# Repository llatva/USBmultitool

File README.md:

# USBmultitool
USB multitool (2 USB ports from HUB, 1xRS232/TTL serial, radio interface w/gpio)

Schematic (analog section): Veli-Matti OH7JEV & Eero OH2BTG & co commenting the schematic at OH2K club

Layout design : Lasse OH3HZB (me)

Licensed under CC-BY 4.0, see https://creativecommons.org/licenses/by/4.0/

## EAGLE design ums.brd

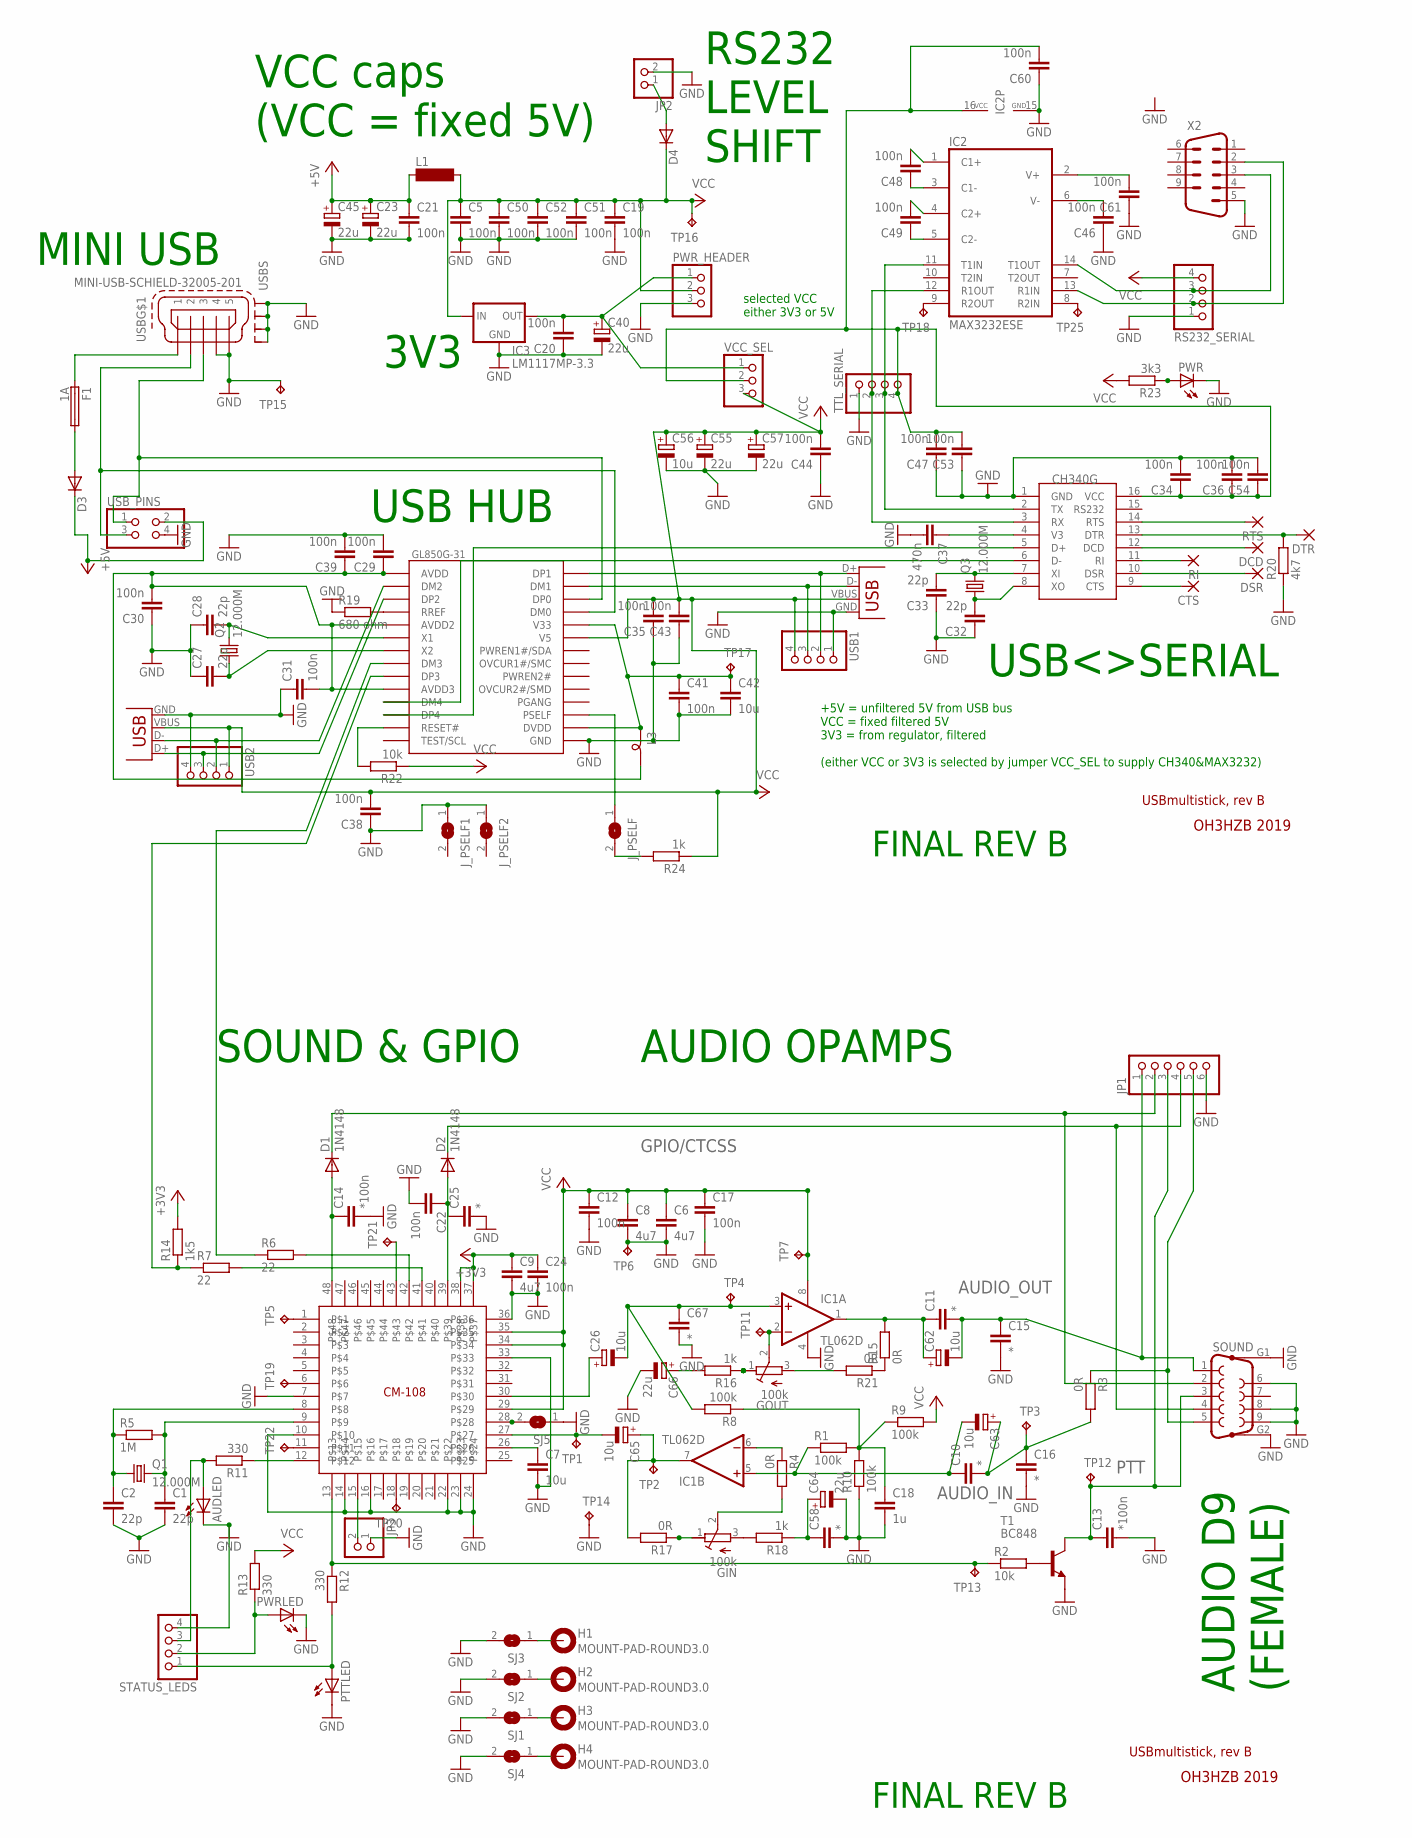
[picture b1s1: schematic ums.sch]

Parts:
AUDLED: LED3MM
C1, C2, C27, C28, C32, C33: 22p; C1206K
C5, C12: 100n; C1206K
C6, C8, C9: 4u7; C1206K
C7: 10u; C1206K
C10, C11, C16, C58: *; C1206K
C13, C14: *100n; C1206K
C15, C25, C67: *; C0805
C17, C19, C20, C21, C22, C24, C29, C30, C34, C35, C36, C38, C39, C41, C43, C44, C46, C47, C48, C49, C50, C51, C52, C53, C60, C61: 100n; C0805
C18: 1u; C4532
C23, C45: 22u; D/7343-31W
C26, C62, C63, C65: 10u; 153CLV-0605
C31, C54: 100n; C1206
C37: 470n; C0805
C40: 22u; SMC_B
C42: 10u; C0805
C55: 22u; C/6032-28R
C56: 10u; SMC_B
C57: 22u; CT6032
C64, C66: 22u; 153CLV-0605
CTS: SMD2; SMD1,27-2,54
D1: 1N4148; SOD123
D2: 1N4148; SOD323-W
D3, D4: DIODE-DO214AC; DO214AC
DCD: SMD2; SMD1,27-2,54
DSR: SMD2; SMD1,27-2,54
DTR: SMD2; SMD1,27-2,54
F1: 1A; TE5
GIN: 100k; RTRIMT93YA
GOUT: 100k; RTRIMT93YA
H1, H2, H3, H4: MOUNT-PAD-ROUND3.0; 3,0-PAD
IC1: TL062D; SO08
IC2: MAX3232ESE; SO16
IC3: LM1117MP-3.3; SOT223
IC4: GL850G-31; TSSOP28
JP1: PINHD-1X6; 1X06
JP2, JP3: PINHD-1X2; 1X02
J_PSELF, J_PSELF1, J_PSELF2: SJ
L1: SM-1206
L3: SM-B5
PTTLED: LED3MM
PWR: LEDCHIPLED_0805; CHIPLED_0805
PWRLED: LED3MM
PWR_HEADER: PINHD-1X3; 1X03
Q1, Q2, Q3: 12.000M; SM49
R1, R8, R9, R10: 100k; R1206
R2, R22: 10k; R1206
R3, R4, R15, R17, R21: 0R; R1206
R5: 1M; R1206
R6, R7: 22; R1206
R11, R12, R13: 330; R1206
R14: 1k5; R1206
R16, R18: 1k; R1206
R19: 680 ohm; R0805
R20: 4k7; R0805
R23: 3k3; R0805
R24: 1k; R0805
RI: SMD2; SMD1,27-2,54
RS232_SERIAL: PINHD-1X4; 1X04
RTS: SMD2; SMD1,27-2,54
SJ1, SJ2, SJ3, SJ4, SJ5: SJ
SOUND: F09HP
STATUS_LEDS: PINHD-1X4; 1X04
T1: BC848; SOT23-BEC
TP1, TP2, TP3, TP4, TP5, TP6, TP7, TP11, TP12, TP13, TP14, TP15, TP16, TP17, TP18, TP19, TP20, TP21, TP22, TP25: TPB1,27; B1,27
TTL_SERIAL: PINHD-1X4; 1X04
U$1: CM-108; LQFP-48
U$6: CH340G; SOIC16
USB: MINI-USB-SCHIELD-32005-201; 32005-201
USB1, USB2: PINHD-1X4; 1X04
USB-P1, USB-P2: USB-A-H
USB_PINS: PINHD-2X2; 2X02
VCC_SEL: PINHD-1X3; 1X03
X2: M09HP

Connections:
+3V3: C9.1, C24.1, R14.2, U$1.37, U$1.38
+5V: C21.1, C23.+, C45.+, D3.C, L1.1, USB_PINS.2
AUDIO_IN: C10.2, C16.1, C63.+, R3.2, TP3.TP
AUDIO_OUT: C11.2, C15.1, C62.-, JP1.1, SOUND.1
CM108-USB-DMINUS: IC4.8 (DM3), R6.1
CM108-USB-DPLUS: IC4.9 (DP3), R7.1, R14.1
GND: AUDLED.K (C), C1.2, C2.2, C5.2, C6.2, C7.2, C8.2, C9.2, C12.2, C13.2, C14.2, C15.2, C16.2, C17.2, C18.2, C19.2, C20.1, C21.2, C22.2, C23.-, C24.2, C25.2, C27.1, C28.1, C29.2, C30.1, C31.1, C32.1, C33.1, C34.2, C35.1, C36.2, C37.2, C38.1, C39.2, C40.-, C41.2, C42.2, C43.1, C44.1, C45.-, C46.1, C47.1, C50.2, C51.2, C52.2, C53.1, C54.2, C55.-, C56.-, C57.-, C58.2, C60.1, C61.1, C64.-, C66.-, C67.2, IC1.4 (V-), IC2.15 (GND), IC3.1 (GND), IC4.15 (GND), JP1.6, JP2.2, JP3.1, J_PSELF1.1, J_PSELF2.1, PTTLED.K (C), PWR.C, PWRLED.K (C), PWR_HEADER.3, R10.1, R19.1, R20.1, RS232_SERIAL.1, SJ1.2, SJ2.2, SJ3.2, SJ4.2, SJ5.1, SOUND.6, SOUND.8, SOUND.9, SOUND.G1, SOUND.G2, STATUS_LEDS.4, T1.E, TP6.TP, TP14.TP, TP15.TP, TTL_SERIAL.1, U$1.7, U$1.10, U$1.14, U$1.16, U$1.22, U$1.23, U$1.24, U$1.33, U$1.36, U$6.1 (GND), USB.4, USB.5, USB.M1 (S1), USB.M2 (S2), USB.M3 (S3), USB.M4 (S4), USB1.1, USB2.4, USB-P1.GND, USB-P2.GND, USB_PINS.4, X2.5
GPIO/CTCSS: D2.C, JP1.4, SOUND.4
JUMPER_SELECTED_VCC: C34.1, C36.1, C47.2, C53.2, C54.1, C60.2, IC2.16 (VCC), TTL_SERIAL.4, U$6.16 (VCC), VCC_SEL.2
unnamed: IC2.11 (T1IN), TTL_SERIAL.3, U$6.2 (TX)
unnamed: R2.2, T1.B
unnamed: C2.1, Q1.1, R5.1, U$1.8
unnamed: C1.1, Q1.2, R5.2, U$1.9
unnamed: C26.-, C67.1, IC1.3 (+IN), R8.2, TP4.TP
unnamed: C65.+, IC1.7 (OUT), R17.2, TP2.TP
unnamed: JP1.5, R3.1, SOUND.5
unnamed: C46.2, IC2.6 (V-)
unnamed: IC4.13 (RESET#), R22.2
unnamed: C65.-, TP1.TP, U$1.27
unnamed: C26.+, U$1.30
unnamed: R2.1, R12.1, TP13.TP, U$1.13
unnamed: IC4.25 (DM0), USB.2, USB_PINS.3
unnamed: C22.1, C25.1, D2.A, U$1.39
unnamed: C11.1, C62.+, IC1.1 (OUT), R15.2
unnamed: R7.2, U$1.41
unnamed: R6.2, U$1.42
unnamed: C14.1, D1.A, U$1.48
unnamed: D1.C, JP1.2, SOUND.2
unnamed: C7.1, U$1.26
unnamed: H2.B3,0, SJ2.1
unnamed: R11.1, U$1.12
unnamed: C18.1, R1.2, R8.1, R9.1, R10.2
unnamed: H1.B3,0, SJ3.1
unnamed: H4.B3,0, SJ4.1
unnamed: C61.2, IC2.2 (V+)
unnamed: AUDLED.A, R11.2, STATUS_LEDS.3
unnamed: SJ5.2, U$1.28
unnamed: PTTLED.A, R12.2, STATUS_LEDS.1
unnamed: JP3.2, U$1.15
unnamed: IC2.12 (R1OUT), TTL_SERIAL.2, U$6.3 (RX)
unnamed: GOUT.2 (S), IC1.2 (-IN), TP11.TP
unnamed: IC1.6 (-IN), R4.1
unnamed: PWR.A, R23.1
unnamed: C28.2, IC4.6 (X1), Q2.2
unnamed: C27.2, IC4.7 (X2), Q2.1
unnamed: D3.A, F1.2
unnamed: R15.1, R21.1
unnamed: GOUT.1 (A), R16.1
unnamed: GIN.1 (A), R17.1
unnamed: C29.1, C30.2, C31.2, C39.1, IC4.1 (AVDD), IC4.5 (AVDD2), IC4.10 (AVDD3), L3.2
unnamed: GIN.2 (S), R4.2
unnamed: GIN.3 (E), R18.2
unnamed: IC4.2 (DM2), USB2.2, USB-P1.D-
unnamed: C32.2, Q3.1, U$6.8 (XO)
unnamed: C33.2, Q3.2, U$6.7 (XI)
unnamed: C37.1, U$6.4 (V3)
unnamed: IC4.3 (DP2), USB2.3, USB-P1.D+
unnamed: H3.B3,0, SJ1.1
unnamed: IC4.12 (DP4), U$6.5 (D+)
unnamed: IC4.11 (DM4), U$6.6 (D-)
unnamed: CTS.1, U$6.9 (CTS)
unnamed: DSR.1, U$6.10 (DSR)
unnamed: RI.1, U$6.11 (RI)
unnamed: DCD.1, U$6.12 (DCD)
unnamed: DTR.1, R20.2, U$6.13 (DTR)
unnamed: RTS.1, U$6.14 (RTS)
unnamed: IC4.28 (DP1), USB1.2, USB-P2.D+
unnamed: IC4.27 (DM1), USB1.3, USB-P2.D-
unnamed: IC2.9 (R2OUT), TP18.TP
unnamed: C20.2, C40.+, IC3.2 (OUT), IC3.4 (OUT), PWR_HEADER.1, VCC_SEL.1
unnamed: IC4.26 (DP0), USB.3, USB_PINS.1
unnamed: TP19.TP, U$1.6
unnamed: IC4.17 (PSELF), J_PSELF.1
unnamed: C41.1, C42.1, IC4.16 (DVDD), IC4.24 (V33), L3.1, TP17.TP
unnamed: TP20.TP, U$1.18
unnamed: IC4.4 (RREF), R19.2
unnamed: IC2.13 (R1IN), RS232_SERIAL.2, X2.2
unnamed: IC2.14 (T1OUT), RS232_SERIAL.3, X2.3
unnamed: D4.A, JP2.1
unnamed: C49.1, IC2.5 (C2-)
unnamed: C49.2, IC2.4 (C2+)
unnamed: C48.1, IC2.3 (C1-)
unnamed: C48.2, IC2.1 (C1+)
unnamed: TP21.TP, U$1.43
unnamed: TP22.TP, U$1.11
unnamed: PWRLED.A, R13.1, STATUS_LEDS.2
unnamed: J_PSELF.2, R24.2
unnamed: IC2.8 (R2IN), TP25.TP
unnamed: F1.1, USB.1
unnamed: C10.1, C63.-, IC1.5 (+IN), R1.1
unnamed: C58.1, C64.+, R18.1
unnamed: C66.+, R16.2
unnamed: TP5.TP, U$1.1
unnamed: GOUT.3 (E), R21.2
PTT: C13.1, JP1.3, SOUND.3, T1.C, TP12.TP
VCC: C5.1, C6.1, C8.1, C12.1, C17.1, C19.1, C35.2, C38.2, C43.2, C44.2, C50.1, C51.1, C52.1, C55.+, C56.+, C57.+, D4.C, IC1.8 (V+), IC3.3 (IN), IC4.23 (V5), L1.2, PWR_HEADER.2, R9.2, R13.2, R22.1, R23.2, R24.1, RS232_SERIAL.4, TP7.TP, TP16.TP, U$1.29, U$1.34, U$1.35, USB1.4, USB2.1, USB-P1.VBUS, USB-P2.VBUS, VCC_SEL.3

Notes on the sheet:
USBmultistick, rev B
OH3HZB 2019
USB HUB
RS232 LEVEL SHIFT
USB<>SERIAL
MINI USB
SOUND & GPIO
AUDIO OPAMPS
AUDIO D9 (FEMALE)
VCC caps (VCC = fixed 5V)
selected VCC either 3V3 or 5V
3V3
+5V = unfiltered 5V from USB bus VCC = fixed filtered 5V 3V3 = from regulator, filtered (either VCC or 3V3 is selected by jumper VCC_SEL to supply CH340&MAX3232)
FINAL REV B

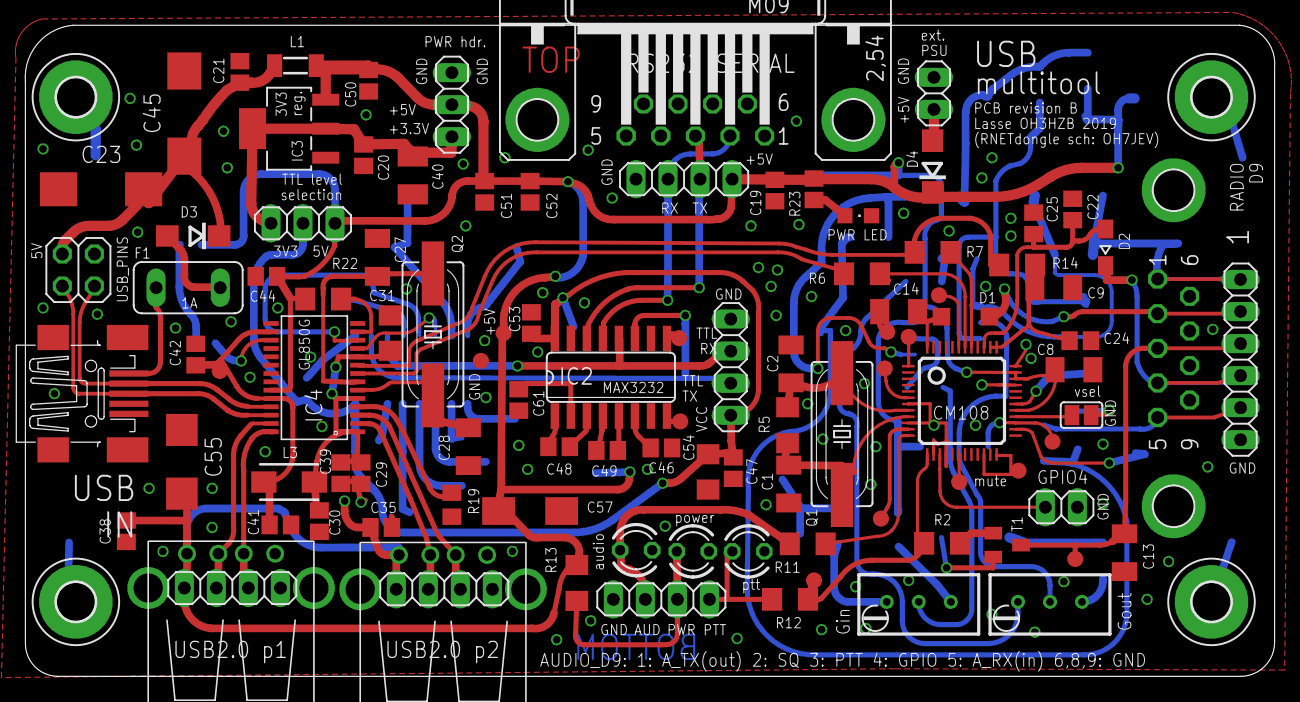
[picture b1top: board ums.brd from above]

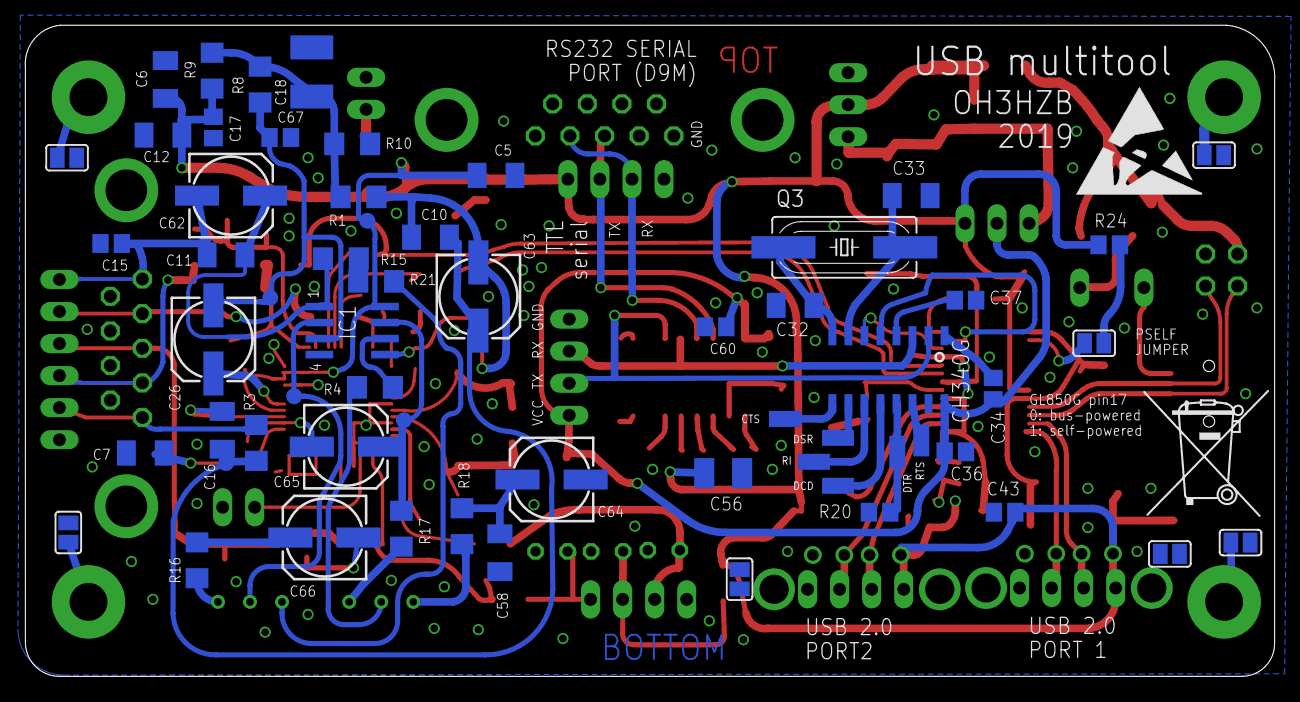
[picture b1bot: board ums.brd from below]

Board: 2 copper layers, 99.0 x 51.6 mm, 167 parts (62 on the bottom side), 96 nets.

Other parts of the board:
U$2: ESD_10.00
U$3: MUELLTONNE_10.00

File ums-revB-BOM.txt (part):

Partlist

Exported from ums.brd at 18.8.2019 14.54

EAGLE Version 7.6.0 Copyright (c) 1988-2016 CadSoft

Assembly variant: 

Part         Value                      Package      Library               Position (mm)         Orientation

AUDLED                                  LED3MM       led                   (49.1 4.1)            R0
C1           22p                        C1206K       resistor              (61.2 9.34)           R270
C2           22p                        C1206K       resistor              (61.38 18.86)         R90
C5           100n                       C1206K       resistor              (62.4 33.8)           MR0
C6           4u7                        C1206K       resistor              (88.6 41.4)           MR90
C7           10u                        C1206K       resistor              (90.2 11.8)           MR180
C8           4u7                        C1206K       resistor              (83.8 18.4)           R0
C9           4u7                        C1206K       resistor              (82.2 24.9)           R0
C10          *                          C1206K       resistor              (67.6 28.9)           MR0
C11          *                          C1206K       resistor              (83.8 27.5)           MR180
C12          100n                       C1206K       resistor              (88.8 37)             MR180
C13          *100n                      C1206K       resistor              (87.8 3.9)            R270
C14          *100n                      C1206K       resistor              (69.9 23)             R180
C15          *                          C0805        resistor              (92.9 28.4)           MR180
C16          *                          C1206K       resistor              (84.1 13.6)           MR90
C17          100n                       C0805        resistor              (84.8 37.6)           MR270
C18          1u                         C1206        resistor              (77 42)               MR90
C19          100n                       C0805        resistor              (60.1 32.6)           R270
C20          100n                       C0805        resistor              (27.5 35.4)           R90
C21          100n                       C0805        resistor              (17.7 42)             R90
C22          100n                       C0805        resistor              (83.7 31.1)           R90
C23          22u                        D/7343-31W   rcl                   (6.7 32.7)            R0
C24          100n                       C0805        resistor              (84.3 20.7)           R0
C25          *                          C0805        resistor              (80.6 30)             R90
C26          10u                        153CLV-0605  rcl                   (84.8 20.8)           MR270
C27          22p                        C1206K       resistor              (28.6 27.3)           R270
C28          22p                        C1206K       resistor              (35.8 12.3)           R90
C29          100n                       C0805        resistor              (27.3 10.2)           R270
C30          100n                       C0805        resistor              (24 6.4)              R90
C31          100n                       C1206        resistor              (29.6 21.3)           R270
C32          22p                        C1206K       resistor              (38.7 23.5)           MR0
C33          22p                        C1206K       resistor              (29.5 32.2)           MR180
C34          100n                       C0805        resistor              (23 16.9)             MR90
C35          100n                       C0805        resistor              (28.9 5.9)            R180
C36          100n                       C0805        resistor              (26 11.9)             MR0
C37          470n                       C0805        resistor              (25.2 23.9)           MR0
C38          100n                       C0805        resistor              (8.7 5.6)             R90
C39          100n                       C0805        resistor              (25.7 10.2)           R270
C40          22u                        SMC_B        rcl                   (31.4 33.8)           R270
C41          100n                       C0805        resistor              (20.9 6.1)            R0
C42          10u                        C0805        resistor              (14.2 19.6)           R90
C43          100n                       C0805        resistor              (22.1 7.1)            MR0
C44          100n                       C0805        resistor              (19.8 25.8)           R0
C45          22u                        D/7343-31W   rcl                   (13.3 38.7)           R270
C46          100n                       C0805        resistor              (51.1 12.2)           R180
C47          100n                       C0805        resistor              (56.8 10.6)           R90
C48          100n                       C0805        resistor              (43 12.3)             R180
C49          100n                       C0805        resistor              (46.8 12)             R180
C50          100n                       C0805        resistor              (27.9 41.3)           R270
C51          100n                       C0805        resistor              (37.1 32.5)           R270
C52          100n                       C0805        resistor              (40.7 32.5)           R270
C53          100n                       C0805        resistor              (40.8 22.1)           R270
C54          100n                       C1206        resistor              (54.8 10.3)           R270
C55          22u                        C/6032-28R   rcl                   (13.1 11.1)           R270
C56          10u                        SMC_B        rcl                   (44.4 10.2)           MR0
C57          22u                        CT6032       rcl                   (40.7 7.2)            R0
C58          *                          C1206K       resistor              (62.1 3.9)            MR270
C60          100n                       C0805        resistor              (45 21.8)             MR0
C61          100n                       C0805        resistor              (39.8 16)             R90
C62          10u                        153CLV-0605  rcl                   (83.4 32.2)           MR0
C63          10u                        153CLV-0605  rcl                   (63.8 24.2)           MR270
C64          22u                        153CLV-0605  rcl                   (58 9.7)              MR180
C65          10u                        153CLV-0605  rcl                   (74.3 12.3)           MR0
C66          22u                        153CLV-0605  rcl                   (76 5.1)              MR180
C67          *                          C0805        resistor              (79.5 36.8)           MR0
CTS                                     SMD1,27-2,54 wirepad               (39.5 14.5)           MR270
D1           1N4148                     SOD123       diode                 (75.2 22.6)           R180
D2           1N4148                     SOD323-W     diode                 (86.3 28.1)           R90
D3                                      DO214AC      diode                 (14 29)               R180
D4                                      DO214AC      diode                 (73.1 32.1)           R90
DCD                                     SMD1,27-2,54 wirepad               (35.3 9.2)            MR270
DSR                                     SMD1,27-2,54 wirepad               (35.3 13)             MR270
DTR                                     SMD1,27-2,54 wirepad               (30.6 11.9)           MR0
F1           1A                         TE5          fuse                  (13.6 24.9)           R0
GIN          100k                       RTRIMT93YA   rcl                   (71.5 0)              R90
GOUT         100k                       RTRIMT93YA   rcl                   (81.9 0)              R90
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
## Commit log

2022-01-07 revB FINAL to Github from local drive
2022-06-07 Create LICENSE, CC-BY 4.0 -- see https://creativecommons.org/licenses/by/4.0/
2023-04-06 remove forgotten gerbers from the project directory
2023-04-06 remove backup files from project directory

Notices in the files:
parts and their libraries:
pimoroni: Licensing: CC v3.0 Share-Alike You are welcome to use this library for commercial purposes.
